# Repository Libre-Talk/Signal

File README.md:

# Signal Mark 0 Hardware

*⛵️ Note that this repository is a work-in-progress. It will be updated and improved on over time.*

This repository contains all of the designs and technical details of the Signal Smart Speaker Prototype.

Each sub-directory represents a prototype device. Currently this consists of:
- [Signal Mark 0](./mk-0) - the first Mark 0 prototype

## Our open hardware principles
* **Copy our designs** – build your own
* **Modify our designs** – remixing is encouraged
* **Always keep the open license** – contribute your output back to the community
* **Credit the original author(s)** – like they do in science

## Feedback or ideas

We are always keen to hear from the community about ways to improve these designs. Whether you're a hacker, maker, engineer, or something else - join us in the:

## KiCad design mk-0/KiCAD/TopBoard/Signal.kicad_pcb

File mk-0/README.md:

# Signal Mk 0 - Prototype

## Kit Major Components
* ESP32-S3
* Mk 0 Motherboard
* Audio Chamber
* Single 10W Speaker with driver
* Elegant 3D printed enclosure
* Universal 12V power supply (USA, EU,UK, AUS, CCC)

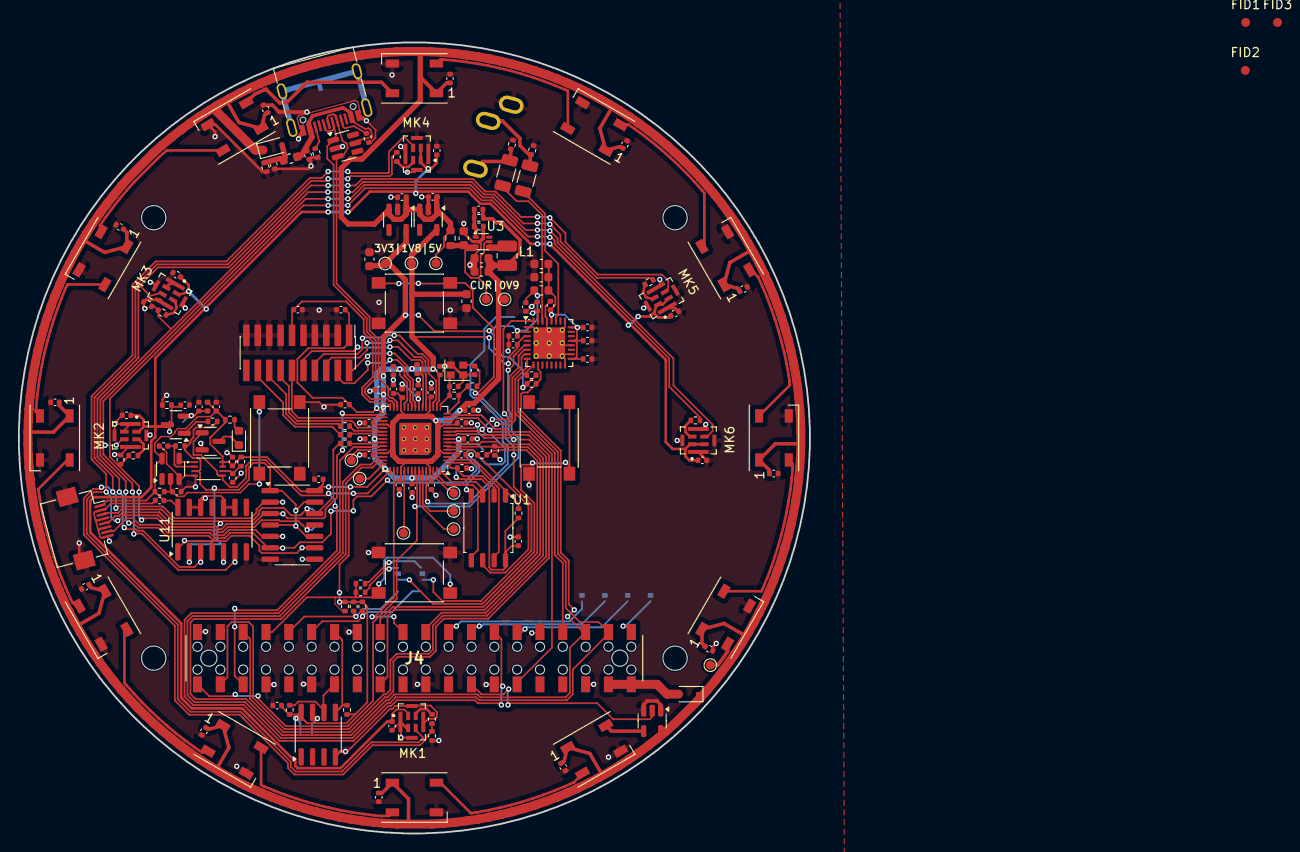
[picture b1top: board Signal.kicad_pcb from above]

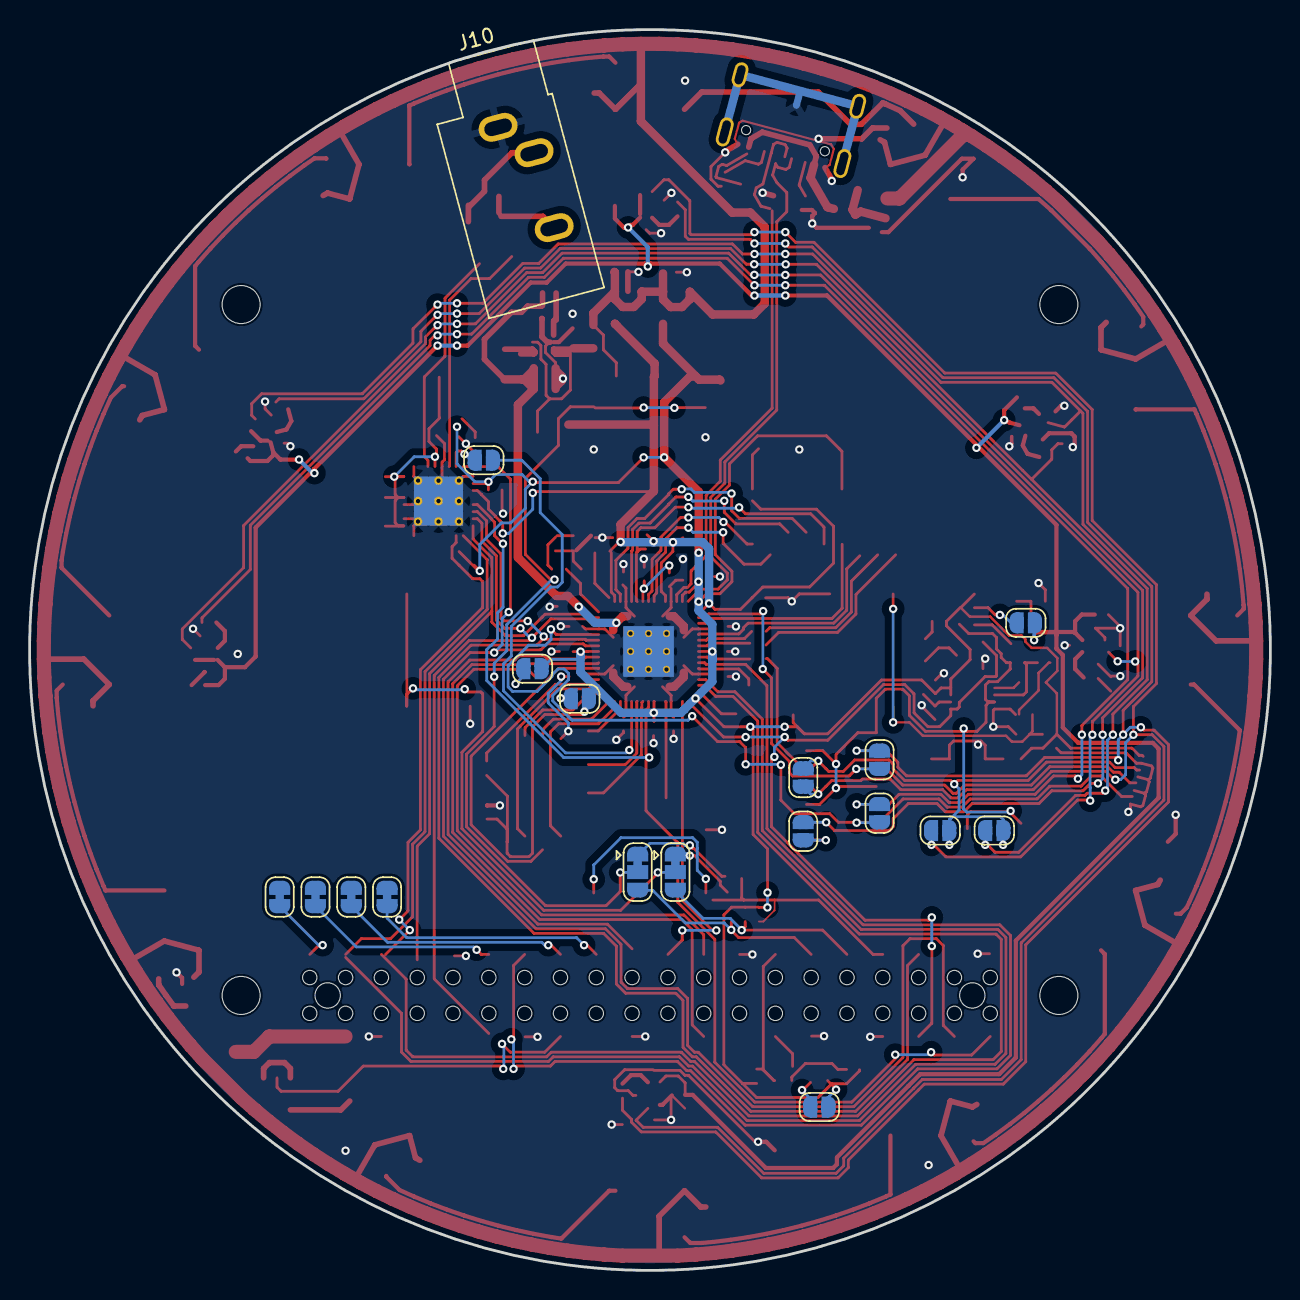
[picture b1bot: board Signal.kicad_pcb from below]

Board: 2 copper layers, 88.0 x 88.0 mm, 202 parts (19 on the bottom side), 116 nets.

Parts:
C1, C5, C6, C7, C8, C9, C16, C17, C18, C19, C20, C21, C22, C23, C25, C27, C28, C29, C31, C36, C37, C38, C39, C40, C41, C45, C46, C47, C48, C49, C52, C53, C54, C55, C56, C58, C59: 100nF; C_0402_1005Metric
C2, C10, C15, C26, C30, C44, C61: 1uF; C_0402_1005Metric
C3, C4: 10pF; C_0402_1005Metric
C11, C34, C35, C42: 4.7uF; C_0603_1608Metric
C12: 10uF; C_0603_1608Metric
C13: 560pF; C_0402_1005Metric
C14, C24: 22uF; C_0603_1608Metric
C32, C33: 47uF; C_1206_3216Metric
C43: 100n; C_0402_1005Metric
C57, C65, C66, C67, C68, C69, C70, C71, C72, C73, C74, C75: 10uF; C_0402_1005Metric
C60: 0.1uF; C_0402_1005Metric
C62: 22pF; C_0402_1005Metric
D1: APT1608; LED_0603_1608Metric
D4, D5: PMEG2010AEH; D_SOD-323F
D6: SRV05-4; SOT-23-6
D7, D8, D9, D10, D11, D12, D13, D14, D15, D16, D17, D18: WS2812B; LED_WS2812B_PLCC4_5.0x5.0mm_P3.2mm
FB1, FB2: 600R; L_0402_1005Metric
FB3, FB4: 120R; L_0603_1608Metric
FID1, FID2, FID3: Fiducial; Fiducial_1mm_Mask2mm
J1: Conn_02x10_Odd_Even; PinHeader_2x10_P1.27mm_Vertical_SMD
J3: Conn_01x08_MountingPin; Hirose_FH12-8S-0.5SH_1x08-1MP_P0.50mm_Horizontal
J4: Conn_02x20_Odd_Even; PinSocket_2x20_P2.54mm_Vertical_Through_SMD
J5: USB_C_Receptacle_USB2.0_16P; USB_C_Receptacle_G-Switch_GT-USB-7010ASV
J10: AudioJack3; Jack_3.5mm_CUI_SJ1-3533NG_Horizontal
JP1, JP2, JP3, JP4, JP5, JP6, JP7, JP8, JP12, JP13: SolderJumper_2_Open; SolderJumper-2_P1.3mm_Open_RoundedPad1.0x1.5mm
JP9, JP10: SolderJumper_3_Bridged12; SolderJumper-3_P1.3mm_Bridged12_RoundedPad1.0x1.5mm
JP11: ID_WP; SolderJumper-2_P1.3mm_Open_RoundedPad1.0x1.5mm
JP23, JP24, JP25, JP26: SolderJumper_2_Bridged; SolderJumper-2_P1.3mm_Bridged_RoundedPad1.0x1.5mm
L1: 1U5; L_1008_2520Metric
MH1, MH2, MH3, MH4: MountingHole_2.7mm_M2.5
MK1, MK2, MK3, MK4, MK5, MK6: GMA4030H11-F26; XDCR_CMM-4030DT-26154-TR
NT1: NetTie_2; NetTie-2_SMD_Pad0.5mm
Q1: NTR4101P; SOT-23
Q2: FDV301N; SOT-23
R1, R3, R4: 4K7; R_0402_1005Metric
R2: 300R; R_0402_1005Metric
R5, R8, R12, R15, R22, R23, R24, R41: 10K; R_0402_1005Metric
R6: 1M; R_0402_1005Metric
R7: 680R; R_0402_1005Metric
R9, R36: 20K; R_0402_1005Metric
R10, R13, R28, R29, R30, R33, R44: 100R; R_0402_1005Metric
R11, R14, R17, R18: 47K; R_0402_1005Metric
R16: 470R; R_0402_1005Metric
R19, R43, R49: 10K(5%); R_0402_1005Metric
R21, R27: 3.9k; R_0402_1005Metric
R25, R26: 6K8; R_0402_1005Metric
R32: 0R1; R_0603_1608Metric
R39, R40: 33R; R_0402_1005Metric
R42: 15K(5%); R_0402_1005Metric
R45: 3.9K(5%); R_0402_1005Metric
R46, R47: 5.1K; R_0402_1005Metric
R48: 330R; R_0402_1005Metric
SW1: SW_Push; SW_SPST_PTS645
SW2: BUTTON 1; SW_SPST_PTS645
SW3: BUTTON 2; SW_SPST_PTS645
SW4: BUTTON 3; SW_SPST_PTS645
TP1, TP3, TP4, TP5, TP6, TP7, TP8, TP9, TP10, TP11, TP13, TP14: TestPoint; TestPoint_Pad_D1.0mm
U1: W25Q64JVSSIQ; SOIC-8_5.23x5.23mm_P1.27mm
U2: XU316-1024-QF60B-C24; QFN-60-1EP_7x7mm_P0.4mm_EP3.6x3.6mm_ThermalVias
U3: AP61102; SOT-563
U4: 74LVC1G17; SOT-23-5
U5: 74LVC2G74; VSSOP-8_2.4x2.1mm_P0.5mm
U6, U11: 74LVC125A; SOIC-14_3.9x8.7mm_P1.27mm
U7: TLV320DAC3101; VQFN-32-1EP_5x5mm_P0.5mm_EP3.5x3.5mm_ThermalVias
U8: NCP114ASN330; TSOT-23-5
U9: NCP114ASN180; TSOT-23-5
U10: CAT24C256; SOIC-8_3.9x4.9mm_P1.27mm
U16: 74AHCT1G125; SOT-23-5
Y1: XRCGB; Crystal_SMD_2016-4Pin_2.0x1.6mm

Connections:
0V9: C13.1, C14.1, C15.1, C16.1, C17.1, C18.1, C19.1, C20.1, C21.1, C22.1, C23.1, C24.1, FB1.1, L1.2, R8.1, TP1.1, U2.4 (VDD), U2.12 (VDD), U2.19 (VDD), U2.27 (VDD), U2.34 (VDD), U2.42 (VDD), U2.49 (VDD), U2.57 (VDD), U2.61 (VDD), U2.62 (VDD), U2.63 (VDD), U2.64 (VDD)
1V8: C6.1, C7.1, C41.1, C42.1, C55.1, C59.1, J1.1, R5.1, TP7.1, U2.17 (VDDIOB18), U2.26 (VDDIOB18), U2.31 (USB_VDD18), U7.3 (DVDD), U9.5 (VOUT)
3V3A: C34.1, C35.1, C36.1, C37.1, C38.1, C39.1, FB4.2, U7.17 (AVDD), U7.21 (SPLVDD), U7.24 (SPRVDD), U7.28 (HPVDD)
+3V3: C1.1, C5.1, C8.1, C9.1, C11.1, C25.1, C31.1, C40.1, C43.1, C49.1, C52.1, C56.1, C58.1, C60.1, FB2.1, FB4.1, J1.11, J3.1, JP5.2 (B), JP6.2 (B), JP11.2 (B), R1.1, R15.1, R16.1, R19.2, R21.1, R25.1, R26.1, R27.1, R36.1, R43.1, R49.1, TP8.1, U1.8 (VCC), U2.8 (VDDIOL), U2.30 (USB_VDD33), U2.38 (VDDIOR), U2.52 (VDDIOT), U4.5 (VCC), U5.7 (~PRE), U5.8 (VCC), U6.14 (VCC), U7.2 (IOVDD), U8.5 (VOUT), U10.8 (VCC), U11.14 (VCC)
+5V: C10.1, C44.1, C57.1, C65.1, C66.1, C67.1, C68.1, C69.1, C70.1, C71.1, C72.1, C73.1, C74.1, C75.1, D4.1 (K), D5.1 (K), D7.1 (VDD), D8.1 (VDD), D9.1 (VDD), D10.1 (VDD), D11.1 (VDD), D12.1 (VDD), D13.1 (VDD), D14.1 (VDD), D15.1 (VDD), D16.1 (VDD), D17.1 (VDD), D18.1 (VDD), R32.1, TP5.1, U8.1 (VIN), U8.3 (EN), U9.1 (VIN), U9.3 (EN), U16.5 (VCC)
/BUT_A: J4.29, JP9.3 (B), R43.2
/BUT_B: J4.31, JP10.3 (B), R49.2
/BUT_C: J4.33, R19.1, R42.1, R45.1, SW4.1
/DAC_RST_N: JP7.1 (A), R24.1, U7.31 (RESET_N)
/I2S_BCLK: J4.12, U2.13 (X1D10), U7.7 (BCLK)
/I2S_DIN: J4.40, U2.53 (X1D34), U7.5 (DIN)
/I2S_DOUT: J4.38, U2.9 (X1D00), U7.32 (GPIO1)
/I2S_LRCK: J4.35, U2.10 (X1D01), U7.6 (WCLK)
/INT_N: J4.13, U2.40 (X0D29)
/MCLK: J4.7, U2.14 (X1D11), U7.8 (MCLK)
/SCL: J4.5, R26.2, U2.44 (X0D37), U7.10 (SCL)
/SDA: J4.3, R25.2, U2.45 (X0D38), U7.9 (SDA)
/SPI_CLK: J4.23, R2.2
/SPI_CS_N: J4.24, R4.2, U2.6 (X0D00)
/SPI_MISO: J4.21, U2.47 (X0D39)
/SPI_MOSI: J4.19, U2.7 (X0D11)
/U_DAC/HPL: C32.1, U7.27 (HPL)
/U_DAC/HPR: C33.1, U7.30 (HPR)
/U_Host/ID_SCL: J4.28, R27.2, U10.6 (SCL)
/U_Host/ID_SDA: J4.27, R21.2, U10.5 (SDA)
/U_Mics Mute/DMIC_CLK_1: JP1.2 (B), MK1.3 (CLOCK), MK4.3 (CLOCK), U6.11
/U_Mics Mute/DMIC_CLK_2: JP2.1 (A), MK2.3 (CLOCK), MK6.3 (CLOCK), U11.6
/U_Mics Mute/DMIC_CLK_3: JP4.1 (A), MK3.3 (CLOCK), MK5.3 (CLOCK), U11.3
/U_Mics Mute/DMIC_IN1: J3.5, JP8.1 (A), U2.32 (X1D13), U6.3
/U_Mics Mute/DMIC_IN1_BUF: JP8.2 (B), R10.2, R13.2, R18.1, U6.2
/U_Mics Mute/DMIC_IN2: J3.7, JP12.1 (A), U2.11 (X1D09), U6.6
/U_Mics Mute/DMIC_IN2_BUF: JP12.2 (B), R14.1, R28.2, R33.2, U6.5
/U_Mics Mute/DMIC_IN3: JP13.1 (A), U6.8
/U_Mics Mute/DMIC_IN3_BUF: JP13.2 (B), R17.1, R29.2, R30.2, U6.9
/U_Mics Mute/MIC_CLK: J3.3, JP1.1 (A), JP2.2 (B), JP4.2 (B), R44.2, U6.12, U11.2, U11.5
/U_Mics Mute/MUTE_DATA: R12.2, R48.2, U5.3 (~Q), U6.1, U6.4, U6.10, U6.13, U11.1, U11.4
/U_Mics Mute/MUTE_PWR: J4.36, Q2.1 (G), U2.46 (X0D40), U5.5 (Q)
/U_XMOS/BOOT_SEL: JP5.1 (A), R3.2
/U_XMOS/QSPI_CLK: R2.1, U1.6 (SCK), U2.5 (X0D10)
/U_XMOS/QSPI_CS_N: R1.2, U1.1 (CS_N), U2.3 (X0D01)
/U_XMOS/QSPI_D0: U1.5 (SI/IO0), U2.59 (X0D04)
/U_XMOS/QSPI_D1: R3.1, U1.2 (SO/IO1), U2.1 (X0D05)
/U_XMOS/QSPI_D2: U1.3 (WP_N/IO2), U2.60 (X0D06)
/U_XMOS/QSPI_D3: U1.7 (HOLD_N/IO3), U2.2 (X0D07)
/U_XMOS/TCK: J1.4, U2.24 (TCK)
/U_XMOS/TDI: J1.8, U2.18 (TDI)
/U_XMOS/TDO: J1.6, U2.20 (TDO)
/U_XMOS/TMS: J1.2, U2.23 (TMS)
/U_XMOS/USB_D_N: D6.3 (IO2), J5.A7 (D-), J5.B7 (D-), U2.28 (USB_DM)
/U_XMOS/USB_D_P: D6.1 (IO1), J5.A6 (D+), J5.B6 (D+), U2.29 (USB_DP)
/U_XMOS/VBUS: C53.1, D6.5 (VP), FB3.1, J5.A4 (VBUS), J5.A9 (VBUS), J5.B4 (VBUS), J5.B9 (VBUS)
/U_XMOS/X0D30: TP4.1, U2.54 (X0D30)
/U_XMOS/X0D31: TP13.1, U2.55 (X0D31)
/U_XMOS/X0D32: JP7.2 (B), U2.56 (X0D32)
/U_XMOS/X0D33: TP10.1, U2.58 (X0D33)
/U_XMOS/X0D35: TP11.1, U2.41 (X0D35)
/U_XMOS/X0D36: TP9.1, U2.43 (X0D36)
/U_XMOS/XL_DN0: J1.14, U2.35 (X1D17)
/U_XMOS/XL_DN1: J1.12, U2.33 (X1D16)
/U_XMOS/XL_UP0: J1.16, R39.2
/U_XMOS/XL_UP1: J1.18, R40.2
/WS2812_CTRL: J4.16, U16.2
/XVF_RST_N: J1.10, R5.2, U2.21 (RST_N)
GND: C1.2, C2.2, C3.2, C4.2, C5.2, C6.2, C7.2, C8.2, C9.2, C10.2, C11.2, C12.2, C14.2, C15.2, C16.2, C17.2, C18.2, C19.2, C20.2, C21.2, C22.2, C23.2, C24.2, C25.2, C26.2, C27.2, C28.2, C29.2, C30.2, C31.2, C34.2, C35.2, C36.2, C37.2, C38.2, C39.2, C40.2, C41.2, C42.2, C43.2, C44.2, C45.2, C46.2, C47.2, C48.2, C49.2, C52.2, C53.2, C54.2, C55.2, C56.2, C57.2, C58.2, C59.2, C60.2, C61.2, C62.2, C65.2, C66.2, C67.2, C68.2, C69.2, C70.2, C71.2, C72.2, C73.2, C74.2, C75.2, D6.2 (VN), D7.3 (VSS), D8.3 (VSS), D9.3 (VSS), D10.3 (VSS), D11.3 (VSS), D12.3 (VSS), D13.3 (VSS), D14.3 (VSS), D15.3 (VSS), D16.3 (VSS), D17.3 (VSS), D18.3 (VSS), J1.3, J1.5, J1.7, J1.9, J1.13, J1.15, J1.17, J1.19, J3.2, J3.4, J3.6, J3.8, J3.MP (MountPin), J4.6, J4.9, J4.14, J4.20, J4.25, J4.30, J4.34, J4.39, J5.A1 (GND), J5.A12 (GND), J5.B1 (GND), J5.B12 (GND), J10.S, MK1.2 (SEL), MK1.5 (GND), MK1.6 (GND), MK1.7 (GND), MK1.8 (GND), MK2.2 (SEL), MK2.5 (GND), MK2.6 (GND), MK2.7 (GND), MK2.8 (GND), MK3.2 (SEL), MK3.5 (GND), MK3.6 (GND), MK3.7 (GND), MK3.8 (GND), MK4.5 (GND), MK4.6 (GND), MK4.7 (GND), MK4.8 (GND), MK5.5 (GND), MK5.6 (GND), MK5.7 (GND), MK5.8 (GND), MK6.5 (GND), MK6.6 (GND), MK6.7 (GND), MK6.8 (GND), NT1.1, Q2.2 (S), R9.2, R11.2, R14.2, R17.2, R18.2, R22.2, R23.2, R24.2, R41.2, R46.2, R47.2, SW1.1, SW2.2, SW3.2, SW4.2, U1.4 (GND), U2.65 (GND), U3.2 (GND), U4.3 (GND), U5.4 (GND), U6.7 (GND), U7.1 (IOVSS), U7.16 (AVSS), U7.18 (DVSS), U7.20 (SPLVSS), U7.25 (SPRVSS), U7.29 (HPVSS), U7.33 (PAD), U8.2 (GND), U9.2 (GND), U10.4 (GND), U11.7 (GND), U11.9, U11.10, U11.12, U11.13, U16.1, U16.3 (GND), Y1.2, Y1.4
unnamed: C4.1, R7.2, Y1.3
unnamed: C30.1, R15.2, SW1.2, U4.2
unnamed: C32.2, J10.T, R23.1
unnamed: C33.2, J10.R, R22.1
unnamed: D1.2 (A), R16.2
unnamed: D1.1 (K), Q2.3 (D)
unnamed: D7.4 (DIN), U16.4
unnamed: D7.2 (DOUT), D8.4 (DIN)
unnamed: D8.2 (DOUT), D9.4 (DIN)
unnamed: D9.2 (DOUT), D10.4 (DIN)
unnamed: D10.2 (DOUT), D11.4 (DIN)
unnamed: D11.2 (DOUT), D12.4 (DIN)
unnamed: D12.2 (DOUT), D13.4 (DIN)
unnamed: D13.2 (DOUT), D14.4 (DIN)
unnamed: D14.2 (DOUT), D15.4 (DIN)
unnamed: D15.2 (DOUT), D16.4 (DIN)
unnamed: D16.2 (DOUT), D17.4 (DIN)
unnamed: D17.2 (DOUT), D18.4 (DIN)
unnamed: D18.2 (DOUT), TP3.1
unnamed: J5.A5 (CC1), R47.1
unnamed: J5.B5 (CC2), R46.1
unnamed: J5.S1 (SHIELD), NT1.2
unnamed: C26.1, FB2.2, JP3.1 (A), Q1.2 (S)
unnamed: JP6.1 (A), R4.1
unnamed: JP9.1 (A), R42.2
unnamed: JP9.2 (C), SW2.1
unnamed: JP10.1 (A), R45.2
unnamed: JP10.2 (C), SW3.1
unnamed: JP11.1 (A), U10.7 (WP)
unnamed: MK1.4 (DATA), R10.1
unnamed: MK2.4 (DATA), R28.1
unnamed: MK3.4 (DATA), R29.1
unnamed: MK4.4 (DATA), R13.1
unnamed: MK5.4 (DATA), R30.1
unnamed: MK6.4 (DATA), R33.1
unnamed: Q1.1 (G), R12.1
unnamed: C2.1, FB1.2, U2.22 (PLL_AVDD)
unnamed: TP14.1, U2.50 (X0D41)
unnamed: R39.1, U2.36 (X1D18)
unnamed: R40.1, U2.37 (X1D19)
unnamed: R44.1, U2.39 (X1D22)
unnamed: C3.1, R6.1, U2.16 (XIN), Y1.1
unnamed: R6.2, R7.1, U2.15 (XOUT)
unnamed: C12.1, R32.2, TP6.1, U3.3 (VIN), U3.5 (EN)
unnamed: C13.2, R8.2, R9.1, U3.1 (FB)
unnamed: L1.1, U3.4 (SW)
unnamed: U4.4, U5.1 (C)
unnamed: C62.1, R48.1, U5.2 (D)
unnamed: C61.1, R36.2, U5.6 (~CLR)
PI_+5V: D5.2 (A), J4.2, J4.4
USB_VBUS: C54.1, D4.2 (A), FB3.2, R41.1
VDD_MIC: C27.1, C28.1, C29.1, C45.1, C46.1, C47.1, C48.1, JP3.2 (B), MK1.1 (VDD), MK2.1 (VDD), MK3.1 (VDD), MK4.1 (VDD), MK4.2 (SEL), MK5.1 (VDD), MK5.2 (SEL), MK6.1 (VDD), MK6.2 (SEL), Q1.3 (D), R11.1

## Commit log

2024-04-16 Trace layout complete
2024-05-23 Create LICENCE
